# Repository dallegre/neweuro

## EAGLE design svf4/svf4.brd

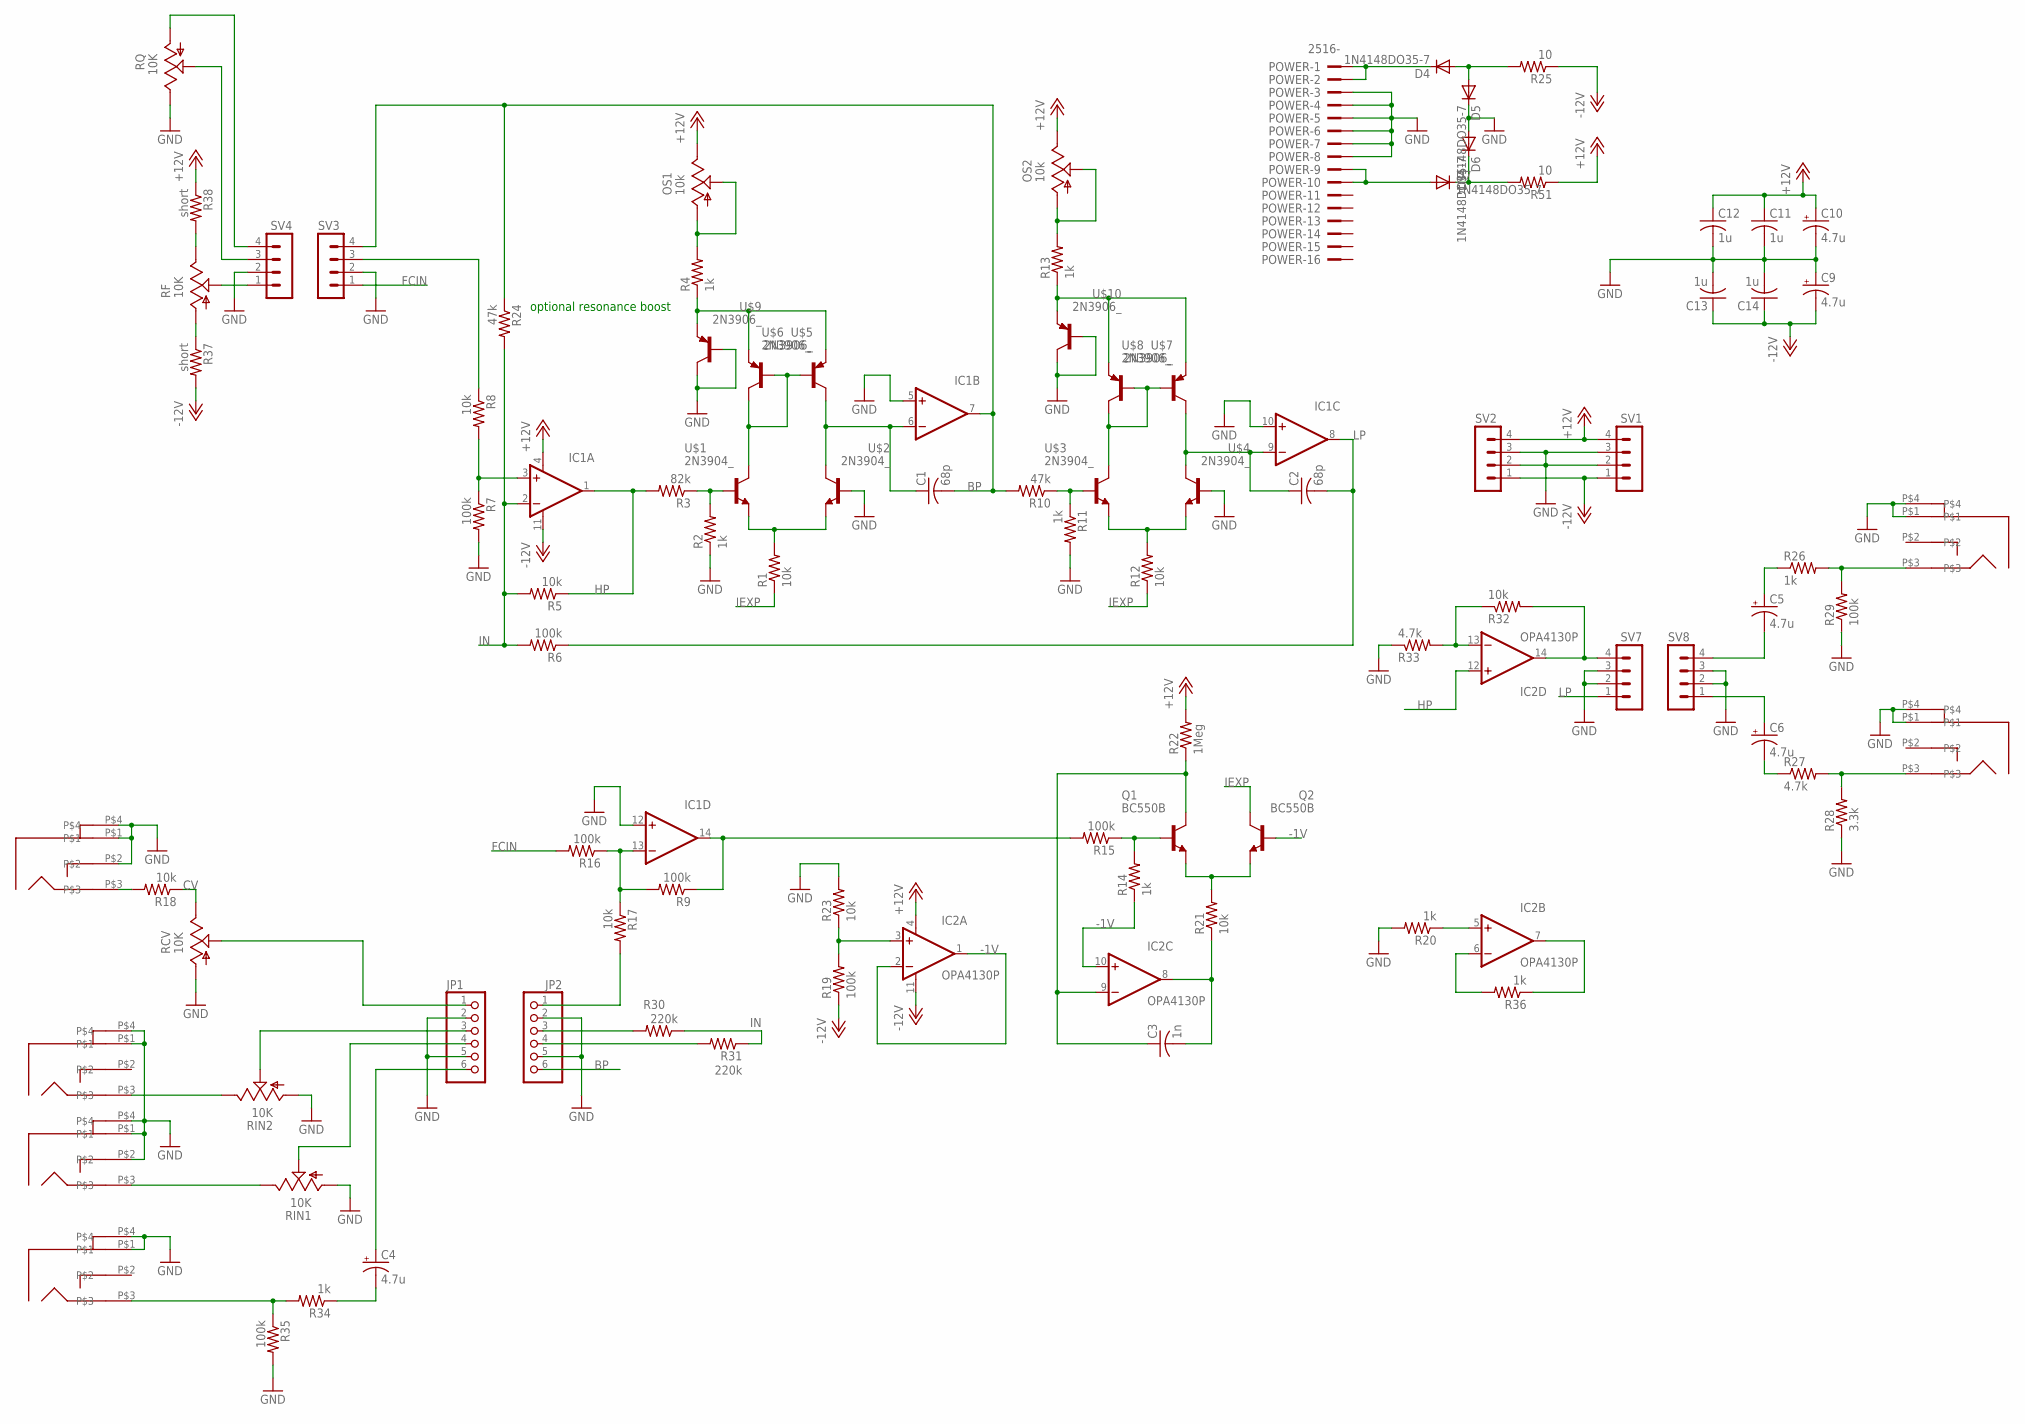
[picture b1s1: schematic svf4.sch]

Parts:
BPOUT: PJ301BM
C1, C2: 68p; C050-025X075
C3: 1n; C050-025X075
C4, C5, C6, C9, C10: 4.7u; E2,5-6
C11, C12, C13, C14: 1u; C050-025X075
CVIN: PJ301BM
D4, D5, D6, D7: 1N4148DO35-7; DO35-7
HPOUT: PJ301BM
IC1, IC2: OPA4130P; DIL14
IN, IN1: PJ301BM
JP1, JP2: PINHD-1X6; 1X06
LPOUT: PJ301BM
OS1, OS2: 10k; S64W
POWER: 2516-; PAK100/2500-16
Q1, Q2: BC550B; TO92-EBC
R1, R5, R8, R12, R17, R21, R23, R32: 10k; 0207/2V
R2, R4, R11, R13, R14, R20, R36: 1k; 0207/2V
R3: 82k; 0207/2V
R6, R7, R9, R15, R16, R19: 100k; 0207/2V
R10, R24: 47k; 0207/2V
R18: 10k; 0204/7
R22: 1Meg; 0207/2V
R25, R51: 10; 0207/2V
R26, R34: 1k; 0204/7
R27: 4.7k; 0204/7
R28: 3.3k; 0204/7
R29, R35: 100k; 0204/7
R30, R31: 220k; 0207/2V
R33: 4.7k; 0207/2V
R37, R38: short; 0204/7
RCV: 10K; EVUFXJ
RF: 10K; EVUFXJ
RIN1, RIN2: 10K; EVUFXJ
RQ: 10K; EVUFXJ
SV1, SV2, SV3, SV4, SV7, SV8: MA04-1
U$1, U$2, U$3, U$4: 2N3904_; TO92-EBC
U$5, U$6, U$7, U$8, U$9, U$10: 2N3906_; TO92-EBC

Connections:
+12V: C10.+, C11.1, C12.1, IC1.4 (V+), IC2.4 (V+), OS1.E, OS2.E, R22.2, R38.1, R51.1, SV1.4, SV2.4
-1V: IC2.1 (OUT), IC2.2 (-IN), IC2.10 (+IN), Q2.B, R14.1
-12V: C9.-, C13.1, C14.1, IC1.11 (V-), IC2.11 (V-), R19.1, R25.1, R37.2, SV1.1, SV2.1
BP: C1.2, IC1.7 (OUT), JP2.6, R10.2, R24.1, SV3.4
CV: R18.1, RCV.3 (E)
FCIN: R16.2, SV3.1
GND: BPOUT.P$1, BPOUT.P$4, C9.+, C10.-, C11.2, C12.2, C13.2, C14.2, CVIN.P$1, CVIN.P$2, CVIN.P$4, D5.C, D6.A, HPOUT.P$1, HPOUT.P$4, IC1.5 (+IN), IC1.10 (+IN), IC1.12 (+IN), IN.P$1, IN.P$2, IN.P$4, IN1.P$1, IN1.P$4, JP1.2, JP1.5, JP2.2, JP2.5, LPOUT.P$1, LPOUT.P$4, POWER.3, POWER.4, POWER.5, POWER.6, POWER.7, POWER.8, R2.1, R7.2, R11.2, R20.2, R23.2, R28.1, R29.1, R33.1, R35.2, RCV.1 (A), RIN1.1 (A), RIN2.1 (A), RQ.3 (E), SV1.2, SV1.3, SV2.2, SV2.3, SV3.2, SV4.2, SV7.2, SV7.3, SV8.2, SV8.3, U$2.B, U$4.B, U$9.B, U$9.E (C), U$10.B, U$10.E (C)
HP: IC1.1 (OUT), IC2.12 (+IN), R3.2, R5.1
IEXP: Q2.C, R1.1, R12.1
IN: IC1.2 (-IN), R5.2, R6.2, R24.2, R30.1, R31.1
LP: C2.2, IC1.8 (OUT), R6.1, SV7.1
LPOUT: LPOUT.P$3, R27.2, R28.2
unnamed: R12.2, U$3.C (E), U$4.C (E)
unnamed: OS1.A, OS1.S, R4.2
unnamed: R4.1, U$5.C (E), U$6.C (E), U$9.C (E)
unnamed: U$1.E (C), U$5.B, U$5.E (C), U$6.B
unnamed: R1.2, U$1.C (E), U$2.C (E)
unnamed: R2.2, R3.1, U$1.B
unnamed: IC2.7 (OUT), R36.1
unnamed: C6.+, SV8.1
unnamed: IC1.3 (+IN), R7.1, R8.2
unnamed: OS2.A, OS2.S, R13.2
unnamed: C1.1, IC1.6 (-IN), U$2.E (C), U$6.E (C)
unnamed: R8.1, SV3.3
unnamed: IC1.13 (-IN), R9.2, R16.1, R17.1
unnamed: U$3.E (C), U$7.B, U$7.E (C), U$8.B
unnamed: R10.1, R11.1, U$3.B
unnamed: JP2.1, R17.2
unnamed: R13.1, U$7.C (E), U$8.C (E), U$10.C (E)
unnamed: C2.1, IC1.9 (-IN), U$4.E (C), U$8.E (C)
unnamed: RF.2 (S), SV4.1
unnamed: D4.A, D5.A, R25.2
unnamed: Q1.B, R14.2, R15.1
unnamed: IC1.14 (OUT), R9.1, R15.2
unnamed: CVIN.P$3, R18.2
unnamed: Q1.E, Q2.E, R21.2
unnamed: RQ.1 (A), SV4.4
unnamed: C3.2, IC2.8 (OUT), R21.1
unnamed: D6.C, D7.C, R51.2
unnamed: C3.1, IC2.9 (-IN), Q1.C, R22.1
unnamed: IC2.3 (+IN), R19.2, R23.1
unnamed: JP1.1, RCV.2 (S)
unnamed: RQ.2 (S), SV4.3
unnamed: C5.-, SV8.4
unnamed: JP1.4, RIN1.2 (S)
unnamed: IN.P$3, RIN1.3 (E)
unnamed: HPOUT.P$3, R26.2, R29.2
unnamed: C4.+, JP1.6
unnamed: JP2.3, R30.2
unnamed: BPOUT.P$3, R34.2, R35.1
unnamed: IN1.P$3, RIN2.3 (E)
unnamed: JP1.3, RIN2.2 (S)
unnamed: IC2.14 (OUT), R32.2, SV7.4
unnamed: IC2.13 (-IN), R32.1, R33.2
unnamed: C6.-, R27.1
unnamed: C5.+, R26.1
unnamed: C4.-, R34.1
unnamed: JP2.4, R31.2
unnamed: IC2.5 (+IN), R20.1
unnamed: IC2.6 (-IN), R36.2
unnamed: R38.2, RF.3 (E)
unnamed: R37.1, RF.1 (A)
unnamed: D7.A, POWER.9, POWER.10
unnamed: D4.C, POWER.1, POWER.2

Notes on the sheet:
optional resonance boost

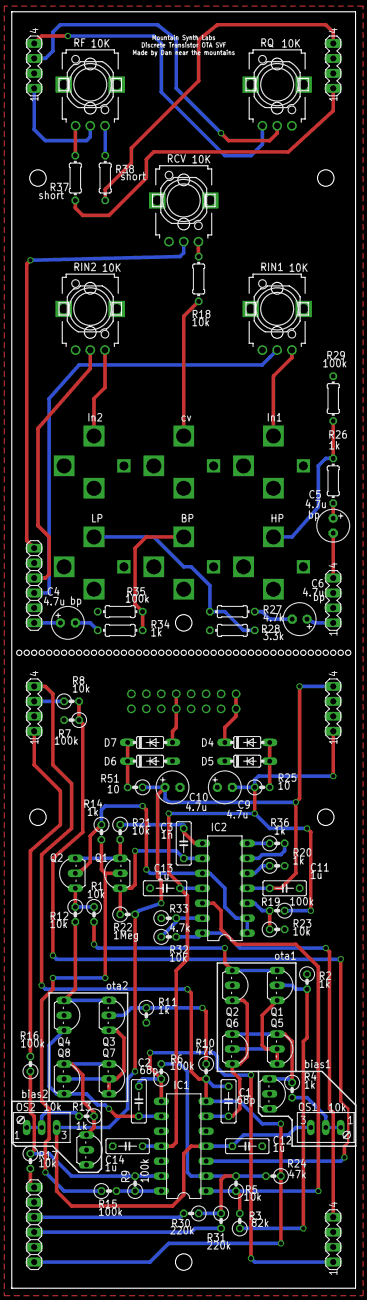
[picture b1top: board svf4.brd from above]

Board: 2 copper layers, 58.4 x 216.8 mm, 91 parts (1 on the bottom side), 64 nets.

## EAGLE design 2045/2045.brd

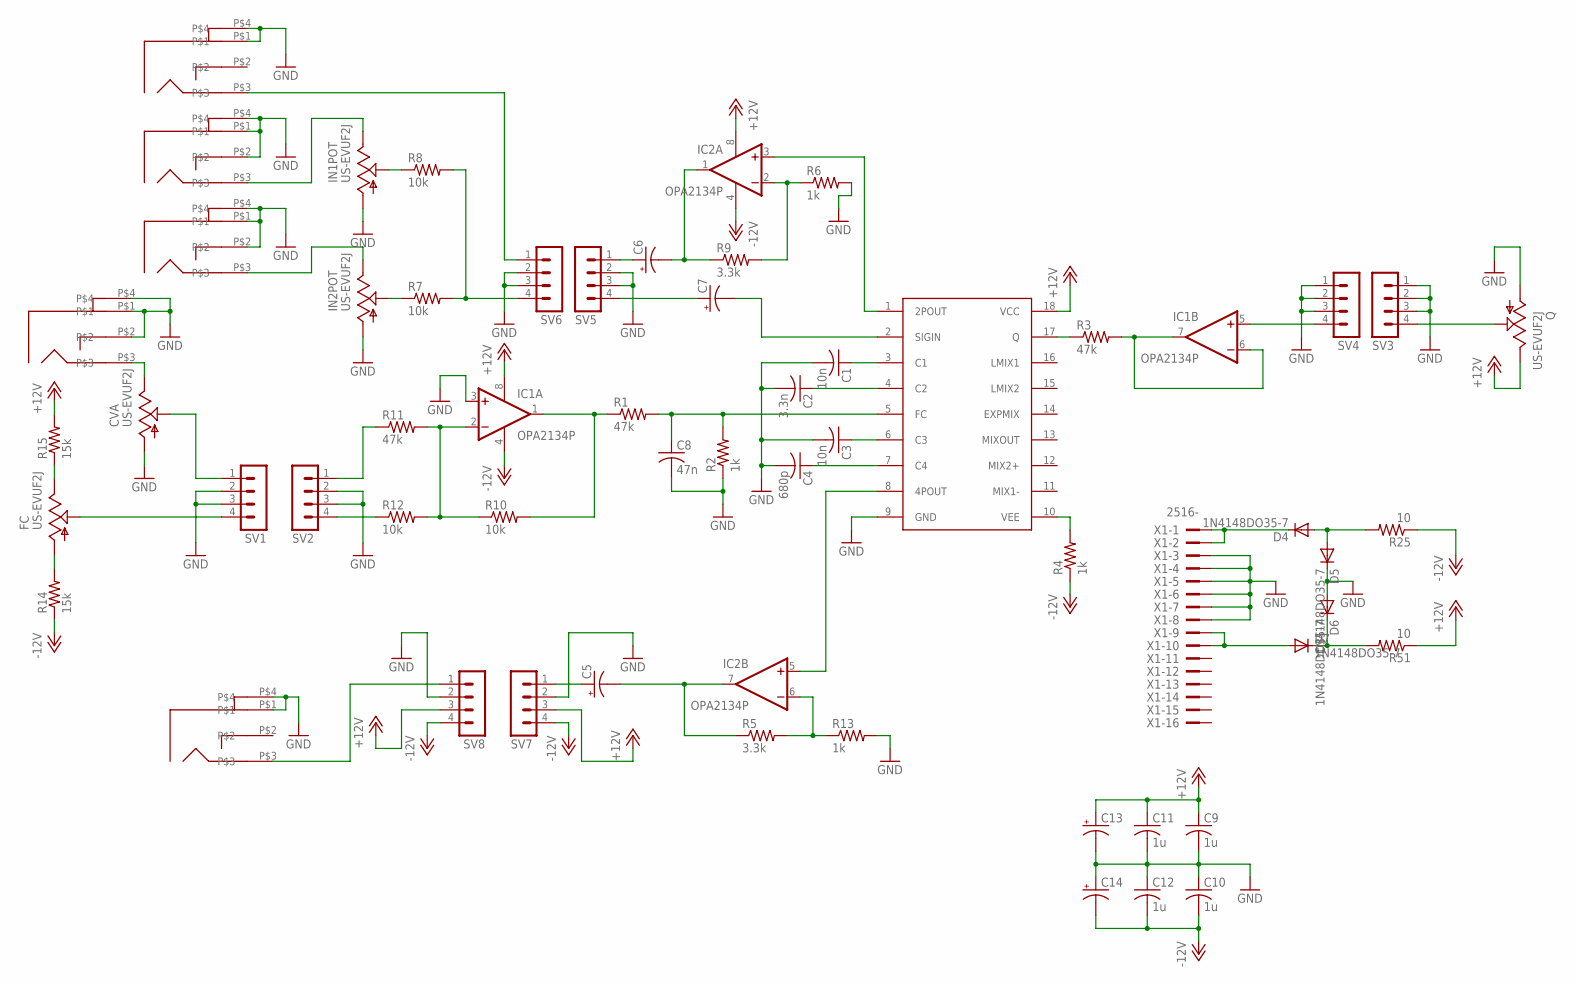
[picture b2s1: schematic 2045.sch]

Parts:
2POUT, 4POUTPUT: PJ301BM
C1, C3: 10n; C050-025X075
C2: 3.3n; C050-025X075
C4: 680p; C050-025X075
C5, C6, C7, C13, C14: CPOL-USE2.5-7; E2,5-7
C8: 47n; C050-025X075
C9, C10, C11, C12: 1u; C050-025X075
CVA: US-EVUF2J; EVUFXJ
CVIN: PJ301BM
D4, D5, D6, D7: 1N4148DO35-7; DO35-7
FC: US-EVUF2J; EVUFXJ
IC1, IC2: OPA2134P; DIL08
IN, IN2: PJ301BM
IN1POT, IN2POT: US-EVUF2J; EVUFXJ
Q: US-EVUF2J; EVUFXJ
R1, R3, R11: 47k; 0204/7
R2, R4, R6, R13: 1k; 0204/7
R5, R9: 3.3k; 0204/7
R7, R8, R10, R12: 10k; 0204/7
R14, R15: 15k; 0204/7
R25, R51: 10; 0207/2V
SV1, SV2, SV3, SV4, SV5, SV6, SV7, SV8: MA04-1
U$1: SSM2045; DIL18
X1: 2516-; PAK100/2500-16

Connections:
+12V: C9.1, C11.1, C13.+, IC1.8 (V+), IC2.8 (V+), Q.3 (E), R15.2, R51.1, SV7.3, SV8.3, U$1.18 (VCC)
-12V: C10.2, C12.2, C14.-, IC1.4 (V-), IC2.4 (V-), R4.1, R14.1, R25.1, SV7.4, SV8.4
GND: 2POUT.P$1, 2POUT.P$4, 4POUTPUT.P$1, 4POUTPUT.P$4, C1.2, C2.2, C3.2, C4.2, C8.2, C9.2, C10.1, C11.2, C12.1, C13.-, C14.+, CVA.1 (A), CVIN.P$1, CVIN.P$2, CVIN.P$4, D5.C, D6.A, IC1.3 (+IN), IN.P$1, IN.P$2, IN.P$4, IN1POT.1 (A), IN2.P$1, IN2.P$2, IN2.P$4, IN2POT.1 (A), Q.1 (A), R2.1, R6.2, R13.2, SV1.2, SV1.3, SV2.2, SV2.3, SV3.1, SV3.2, SV3.3, SV4.1, SV4.2, SV4.3, SV5.2, SV5.3, SV6.2, SV6.3, SV7.2, SV8.2, U$1.9 (GND), X1.3, X1.4, X1.5, X1.6, X1.7, X1.8
unnamed: C1.1, U$1.3 (C1)
unnamed: C2.1, U$1.4 (C2)
unnamed: C3.1, U$1.6 (C3)
unnamed: C4.1, U$1.7 (C4)
unnamed: FC.2 (S), SV1.4
unnamed: FC.1 (A), R14.2
unnamed: FC.3 (E), R15.1
unnamed: C8.1, R1.2, R2.2, U$1.5 (FC)
unnamed: R3.1, U$1.17 (Q)
unnamed: R4.2, U$1.10 (VEE)
unnamed: IC2.3 (+IN), U$1.1 (2POUT)
unnamed: IC2.2 (-IN), R6.1, R9.2
unnamed: IC2.5 (+IN), U$1.8 (4POUT)
unnamed: C5.-, IC2.7 (OUT), R5.1
unnamed: IN1POT.2 (S), R8.1
unnamed: C7.-, U$1.2 (SIGIN)
unnamed: R12.1, SV2.4
unnamed: IC1.2 (-IN), R10.1, R11.2, R12.2
unnamed: IC1.1 (OUT), R1.1, R10.2
unnamed: IC1.6 (-IN), IC1.7 (OUT), R3.2
unnamed: R11.1, SV2.1
unnamed: CVA.3 (E), CVIN.P$3
unnamed: Q.2 (S), SV3.4
unnamed: C7.+, SV5.4
unnamed: C6.+, SV5.1
unnamed: 2POUT.P$3, SV6.1
unnamed: R7.2, R8.2, SV6.4
unnamed: C5.+, SV7.1
unnamed: IN2POT.2 (S), R7.1
unnamed: IC1.5 (+IN), SV4.4
unnamed: CVA.2 (S), SV1.1
unnamed: 4POUTPUT.P$3, SV8.1
unnamed: IC2.6 (-IN), R5.2, R13.1
unnamed: C6.-, IC2.1 (OUT), R9.1
unnamed: IN.P$3, IN1POT.3 (E)
unnamed: IN2.P$3, IN2POT.3 (E)
unnamed: D6.C, D7.C, R51.2
unnamed: D4.A, D5.A, R25.2
unnamed: D7.A, X1.9, X1.10
unnamed: D4.C, X1.1, X1.2

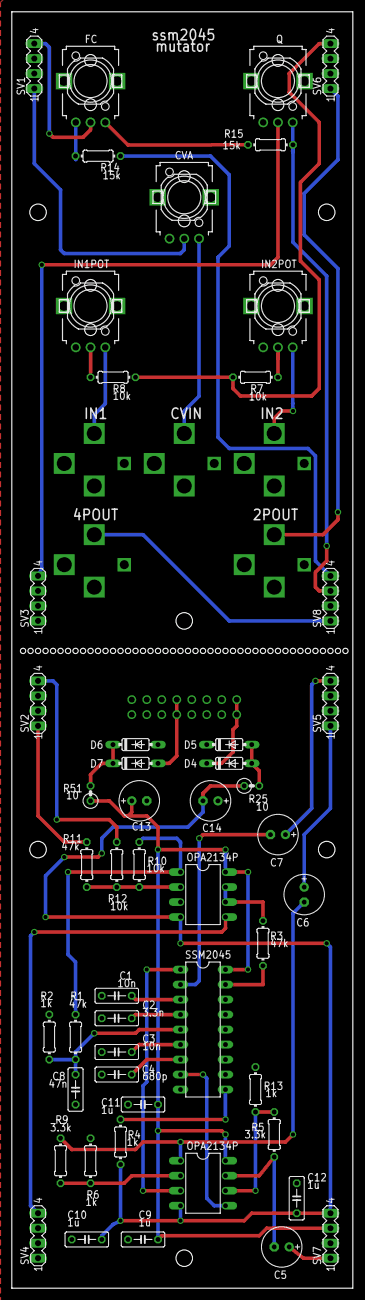
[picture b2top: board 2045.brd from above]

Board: 2 copper layers, 57.8 x 216.2 mm, 57 parts (1 on the bottom side), 43 nets.

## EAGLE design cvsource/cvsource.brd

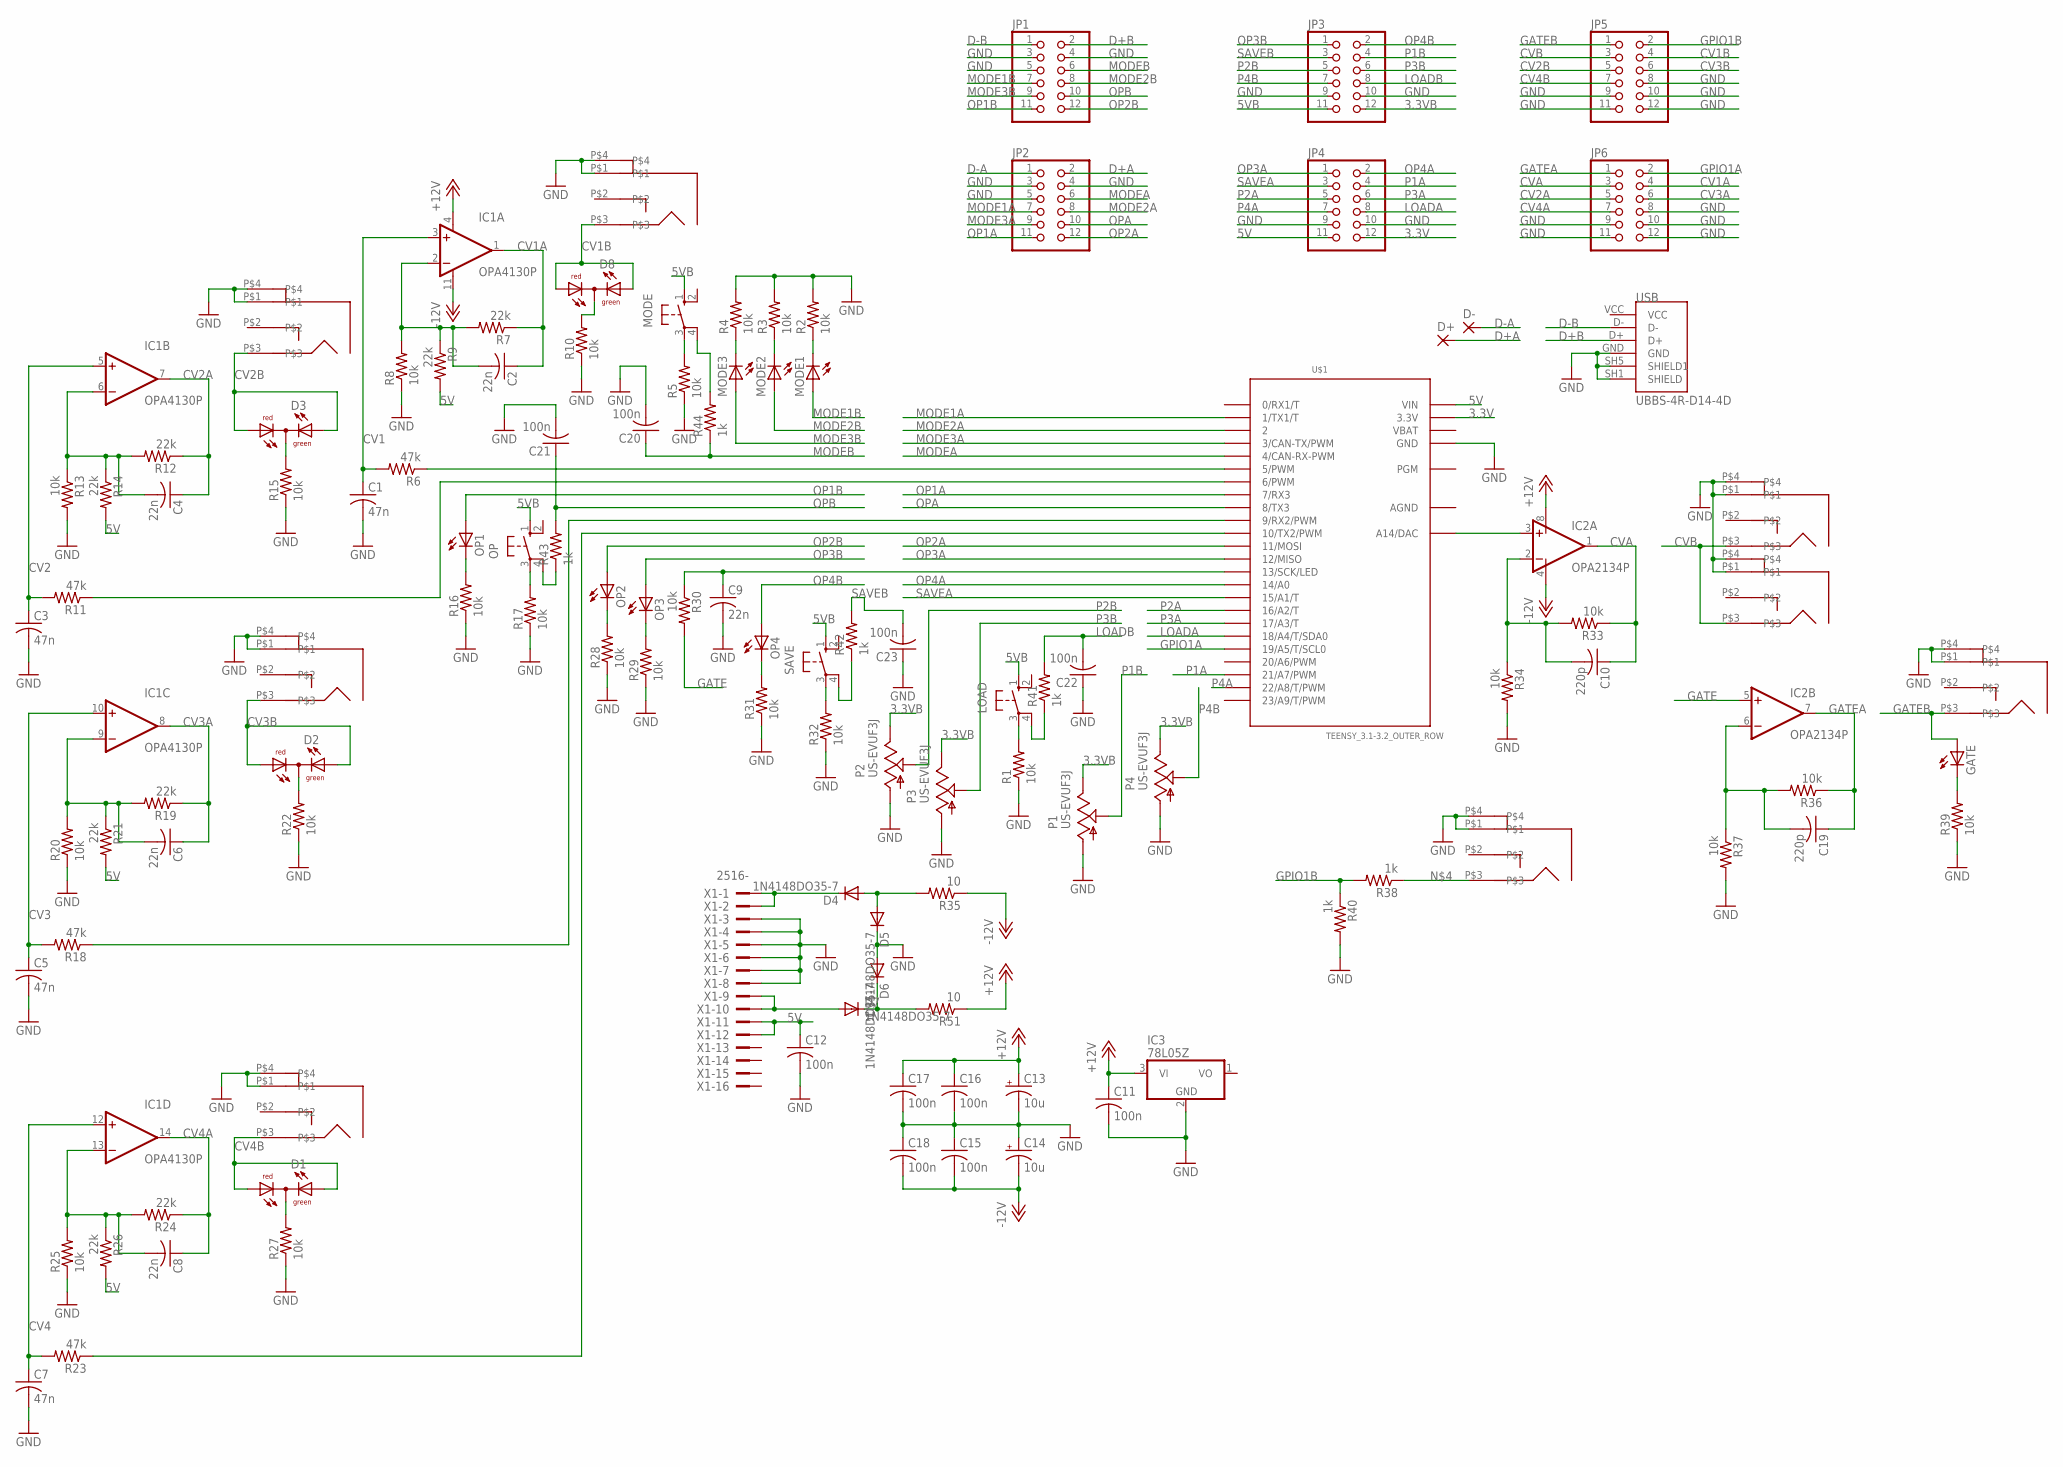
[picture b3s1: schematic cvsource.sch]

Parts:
C1, C3, C5, C7: 47n; C075-032X103
C2, C4, C6, C8, C9: 22n; C075-032X103
C10, C19: 220p; C075-032X103
C11, C12, C15, C16, C17, C18, C20, C21, C22, C23: 100n; C075-032X103
C13, C14: 10u; E5-10,5
CVOUT, CVOUT1, CVOUT2, CVOUT3, CVOUT4, CVOUT5, CVOUT6, CVOUT7: PJ301BM
D1, D2, D3, D8: DUOLED5MM
D4, D5, D6, D7: 1N4148DO35-7; DO35-7
D+: 2,0/0,9-R
D-: 2,0/0,9-R
GATE: LED5MM
IC1: OPA4130P; DIL14
IC2: OPA2134P; DIL08
IC3: 78L05Z; TO92
JP1, JP2, JP3, JP4, JP5, JP6: PINHD-2X6; 2X06
LOAD: 40-XX; B3F-40XX
MODE: 40-XX; B3F-40XX
MODE1, MODE2, MODE3: LED5MM
OP: 40-XX; B3F-40XX
OP1, OP2, OP3, OP4: LED5MM
P1, P2, P3, P4: US-EVUF3J; EVUFXJ
R1, R2, R3, R4, R5, R8, R10, R13, R15, R16, R17, R20, R22, R25, R27, R28, R29, R30, R31, R32, R33, R34, R36, R37, R39: 10k; 0207/2V
R6, R11, R18, R23: 47k; 0207/2V
R7, R9, R12, R14, R19, R21, R24, R26: 22k; 0207/2V
R35, R51: 10; 0207/2V
R38, R40, R41, R42, R43, R44: 1k; 0207/2V
SAVE: 40-XX; B3F-40XX
U$1: TEENSY_3.1-3.2_OUTER_ROW; TEENSY_3.0-3.2&LC_OUTER_ROW
USB: UBBS-4R-D14-4D; JST_UBBS-4R-D14-4D
X1: 2516-; PAK100/2500-16

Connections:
3.3V: JP4.12, U$1.3.3V, U$1.3.3V1 (3.3V)
3.3VB: JP3.12, P1.3 (E), P2.3 (E), P3.3 (E), P4.3 (E)
5V: C12.1, JP4.11, R9.2, R14.2, R21.2, R26.2, U$1.VIN, X1.11, X1.12
5VB: JP3.11, LOAD.1 (S), MODE.1 (S), OP.1 (S), SAVE.1 (S)
+12V: C11.1, C13.+, C16.1, C17.1, IC1.4 (V+), IC2.8 (V+), IC3.3 (VI), R51.1
-12V: C14.-, C15.2, C18.2, IC1.11 (V-), IC2.4 (V-), R35.1
AGND: U$1.AGND
CV1: C1.1, IC1.3 (+IN), R6.2
CV1A: C2.1, IC1.1 (OUT), JP6.4, R7.1
CV1B: CVOUT1.P$3, D8.AG, D8.AR, JP5.4
CV2: C3.1, IC1.5 (+IN), R11.2
CV2A: C4.1, IC1.7 (OUT), JP6.5, R12.1
CV2B: CVOUT2.P$3, D3.AG, D3.AR, JP5.5
CV3: C5.1, IC1.10 (+IN), R18.2
CV3A: C6.1, IC1.8 (OUT), JP6.6, R19.1
CV3B: CVOUT3.P$3, D2.AG, D2.AR, JP5.6
CV4: C7.1, IC1.12 (+IN), R23.2
CV4A: C8.1, IC1.14 (OUT), JP6.7, R24.1
CV4B: CVOUT4.P$3, D1.AG, D1.AR, JP5.7
CVA: C10.1, IC2.1 (OUT), JP6.3, R33.1
CVB: CVOUT.P$3, CVOUT6.P$3, JP5.3
D+A: D+.1, JP2.2
D+B: JP1.2, USB.D+
D-A: D-.1, JP2.1
D-B: JP1.1, USB.D-
GATE: IC2.5 (+IN), R30.2
GATEA: C19.1, IC2.7 (OUT), JP6.1, R36.1
GATEB: CVOUT5.P$3, GATE.A, JP5.1
GND: C1.2, C3.2, C5.2, C7.2, C9.2, C11.2, C12.2, C13.-, C14.+, C15.1, C16.2, C17.2, C18.1, C20.2, C21.2, C22.1, C23.1, CVOUT.P$1, CVOUT.P$4, CVOUT1.P$1, CVOUT1.P$4, CVOUT2.P$1, CVOUT2.P$4, CVOUT3.P$1, CVOUT3.P$4, CVOUT4.P$1, CVOUT4.P$4, CVOUT5.P$1, CVOUT5.P$4, CVOUT6.P$1, CVOUT6.P$4, CVOUT7.P$1, CVOUT7.P$4, D5.C, D6.A, IC3.2 (GND), JP1.3, JP1.4, JP1.5, JP2.3, JP2.4, JP2.5, JP3.9, JP3.10, JP4.9, JP4.10, JP5.8, JP5.9, JP5.10, JP5.11, JP5.12, JP6.8, JP6.9, JP6.10, JP6.11, JP6.12, P1.1 (A), P2.1 (A), P3.1 (A), P4.1 (A), R1.1, R2.2, R3.2, R4.2, R5.1, R8.1, R10.1, R13.2, R15.1, R16.1, R17.1, R20.1, R22.1, R25.1, R27.1, R28.1, R29.1, R31.1, R32.1, R34.2, R37.2, R39.1, R40.2, U$1.GND, U$1.GND1 (GND), USB.GND, USB.SH1 (SHIELD), USB.SH5 (SHIELD1), X1.3, X1.4, X1.5, X1.6, X1.7, X1.8
GPIO1A: JP6.2, U$1.19/A5 (19/A5/T/SCL0)
GPIO1B: JP5.2, R38.2, R40.1
LOADA: JP4.8, U$1.18/A4 (18/A4/T/SDA0)
LOADB: C22.2, JP3.8, R41.2
MODE1A: JP2.7, U$1.1 (1/TX1/T)
MODE1B: JP1.7, MODE1.A
MODE2A: JP2.8, U$1.2
MODE2B: JP1.8, MODE2.A
MODE3A: JP2.9, U$1.3 (3/CAN-TX/PWM)
MODE3B: JP1.9, MODE3.A
MODEA: JP2.6, U$1.4 (4/CAN-RX-PWM)
MODEB: C20.1, JP1.6, R44.1
unnamed: MODE1.K (C), R2.1
unnamed: MODE2.K (C), R3.1
unnamed: MODE3.K (C), R4.1
unnamed: CVOUT7.P$3, R38.1
unnamed: C19.2, IC2.6 (-IN), R36.2, R37.1
unnamed: GATE.K (C), R39.2
unnamed: LOAD.4 (P1), R41.1
unnamed: MODE.3, R5.2
unnamed: R6.1, U$1.5 (5/PWM)
unnamed: OP1.K (C), R16.2
unnamed: C2.2, IC1.2 (-IN), R7.2, R8.2, R9.1
unnamed: R42.1, SAVE.4 (P1)
unnamed: D8.K (C), R10.2
unnamed: R11.1, U$1.6 (6/PWM)
unnamed: C4.2, IC1.6 (-IN), R12.2, R13.1, R14.1
unnamed: OP.4 (P1), R43.1
unnamed: D3.K (C), R15.2
unnamed: MODE.4 (P1), R44.2
unnamed: D1.K (C), R27.2
unnamed: OP.3, R17.2
unnamed: R18.1, U$1.9 (9/RX2/PWM)
unnamed: C6.2, IC1.9 (-IN), R19.2, R20.2, R21.1
unnamed: D2.K (C), R22.2
unnamed: OP4.K (C), R31.2
unnamed: R23.1, U$1.10 (10/TX2/PWM)
unnamed: C8.2, IC1.13 (-IN), R24.2, R25.2, R26.1
unnamed: OP2.K (C), R28.2
unnamed: OP3.K (C), R29.2
unnamed: C9.1, R30.1, U$1.13 (13/SCK/LED)
unnamed: R32.2, SAVE.3
unnamed: LOAD.3, R1.2
unnamed: IC2.3 (+IN), U$1.RESET/DAC (A14/DAC)
unnamed: C10.2, IC2.2 (-IN), R33.2, R34.1
unnamed: D6.C, D7.C, R51.2
unnamed: D4.A, D5.A, R35.2
unnamed: D7.A, X1.9, X1.10
unnamed: D4.C, X1.1, X1.2
OP1A: JP2.11, U$1.7 (7/RX3)
OP1B: JP1.11, OP1.A
OP2A: JP2.12, U$1.11 (11/MOSI)
OP2B: JP1.12, OP2.A
OP3A: JP4.1, U$1.12 (12/MISO)
OP3B: JP3.1, OP3.A
OP4A: JP4.2, U$1.14/A0
OP4B: JP3.2, OP4.A
OPA: JP2.10, U$1.8 (8/TX3)
OPB: C21.1, JP1.10, R43.2
P1A: JP4.4, U$1.21/A7 (21/A7/PWM)
P1B: JP3.4, P1.2 (S)
P2A: JP4.5, U$1.16/A2 (16/A2/T)
P2B: JP3.5, P2.2 (S)
P3A: JP4.6, U$1.17/A3 (17/A3/T)
P3B: JP3.6, P3.2 (S)
P4A: JP4.7, U$1.22/A8 (22/A8/T/PWM)
P4B: JP3.7, P4.2 (S)
SAVEA: JP4.3, U$1.15/A1 (15/A1/T)
SAVEB: C23.2, JP3.3, R42.2
VBAT: U$1.VBAT

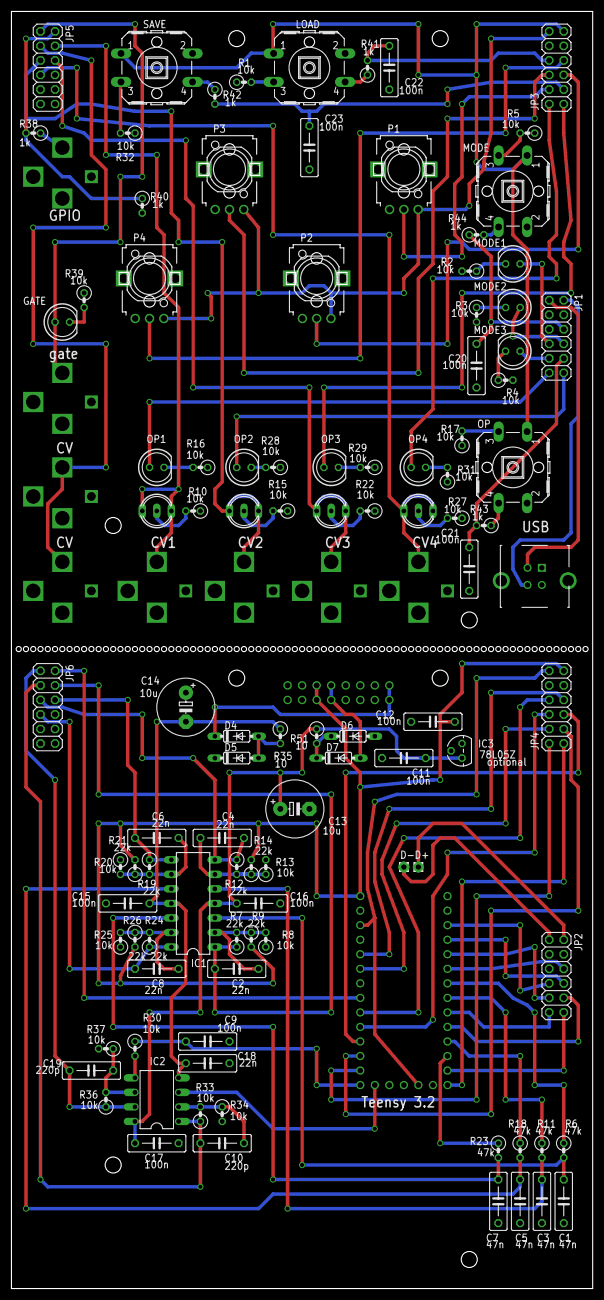
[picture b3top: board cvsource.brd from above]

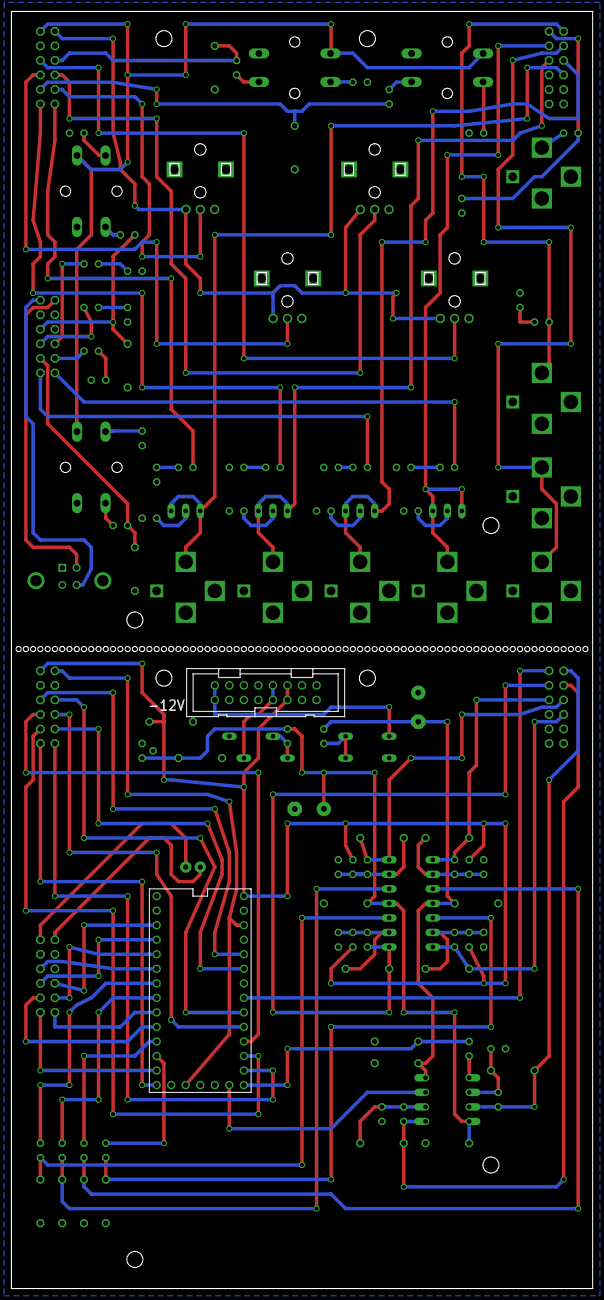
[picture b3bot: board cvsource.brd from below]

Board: 2 copper layers, 101.6 x 223.2 mm, 114 parts (2 on the bottom side), 97 nets.

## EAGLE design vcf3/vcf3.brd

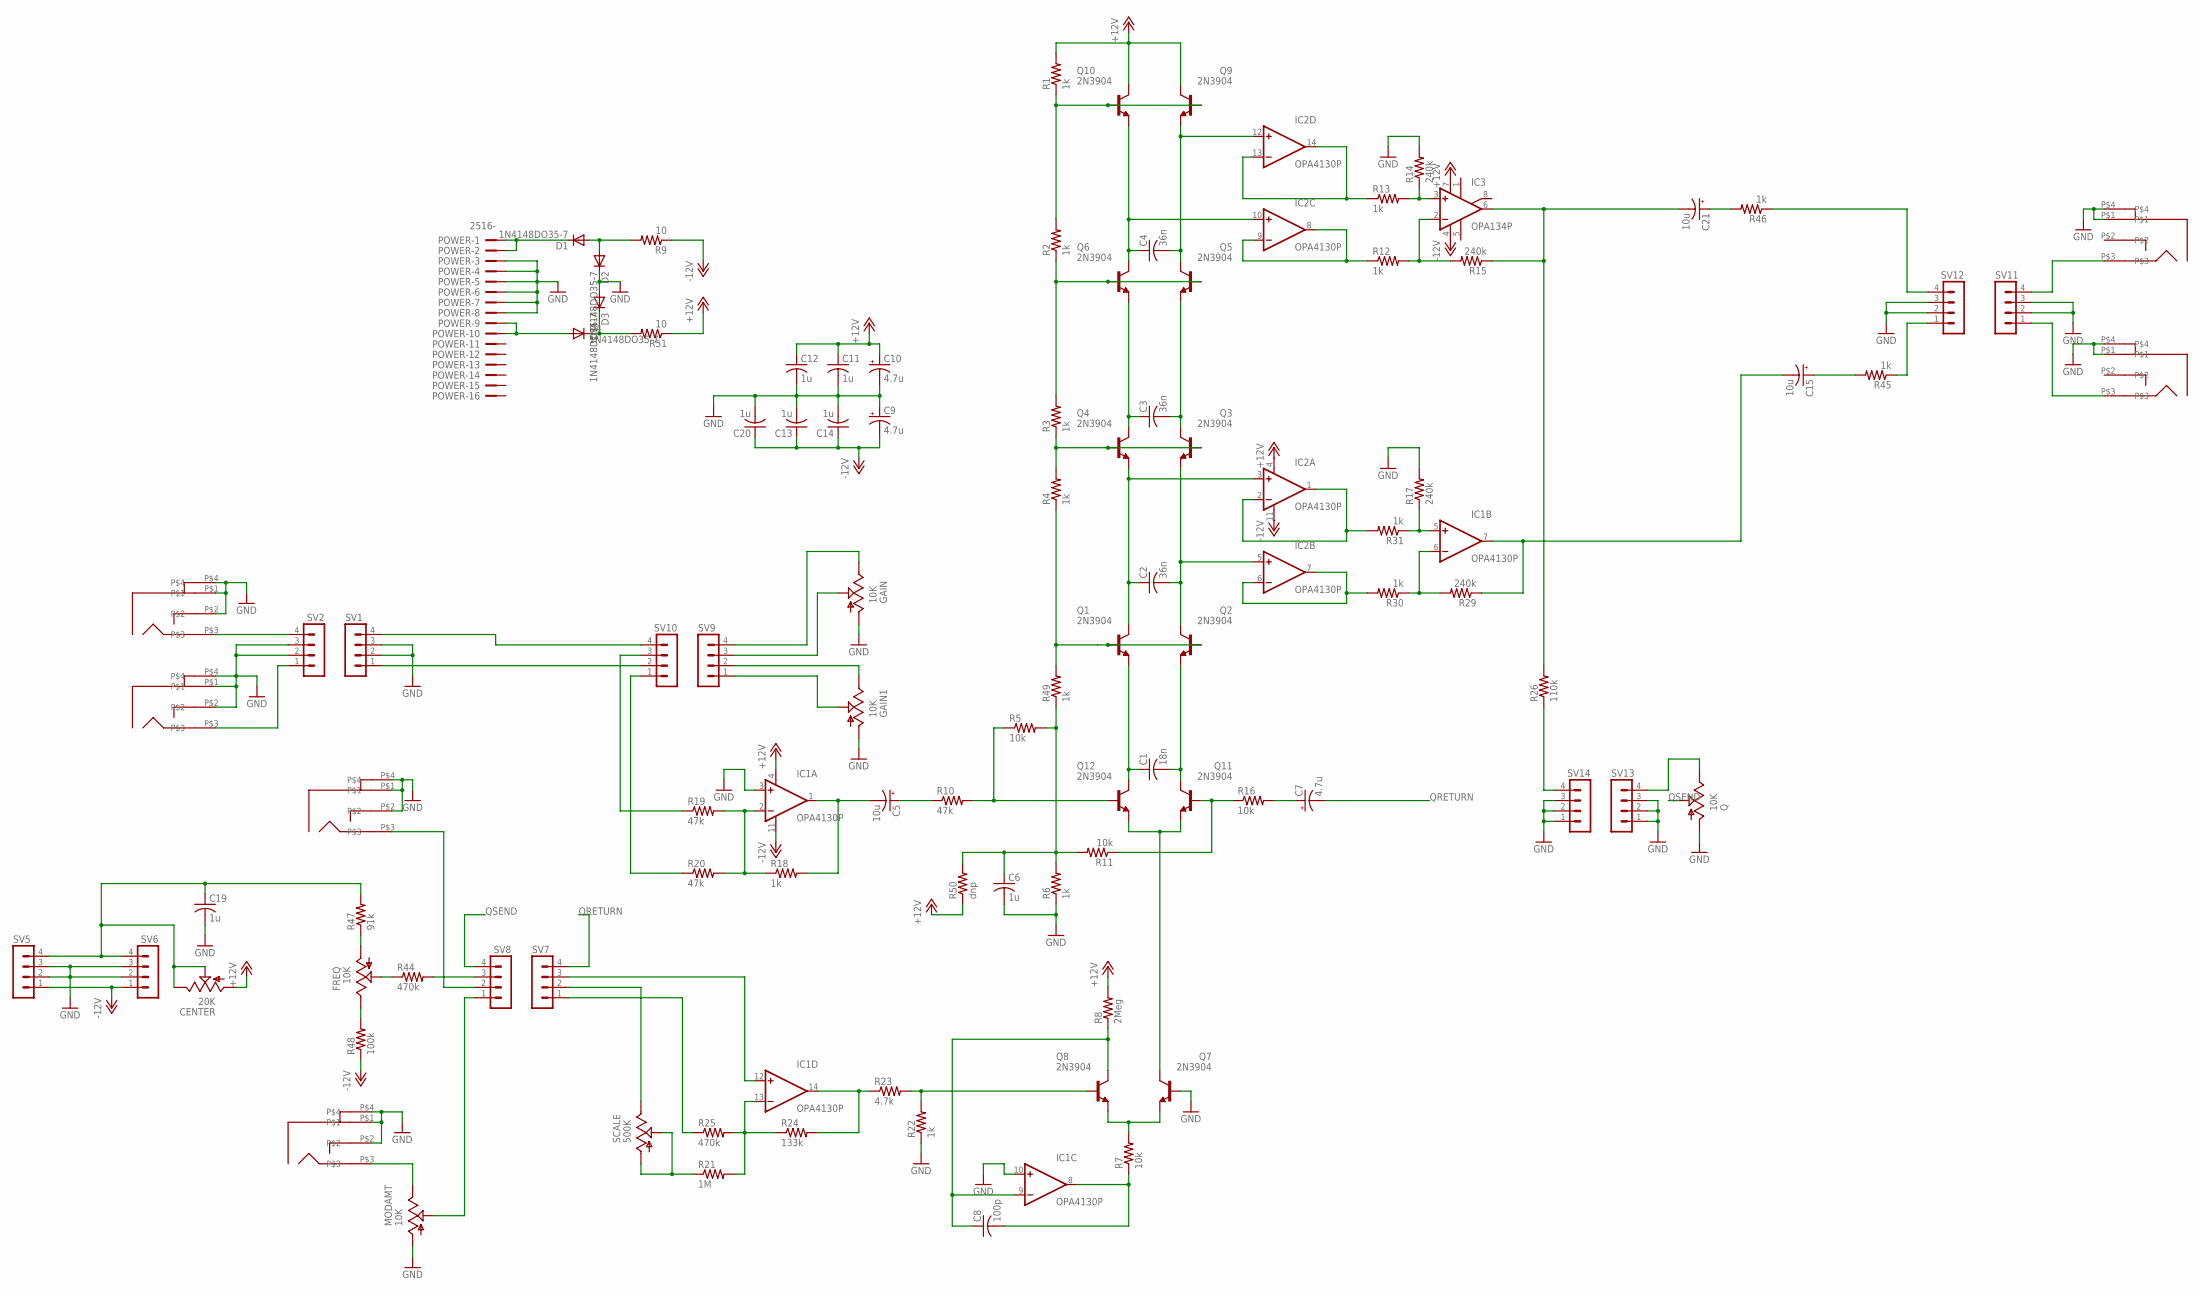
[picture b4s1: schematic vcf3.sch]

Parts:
AIN, AIN2: PJ301BM
BP: PJ301BM
C1: 18n; C050-025X075
C2, C3, C4: 36n; C050-025X075
C5, C15, C21: 10u; E2,5-6
C6, C11, C12, C13, C14, C19, C20: 1u; C050-025X075
C7, C9, C10: 4.7u; E2,5-6
C8: 100p; C050-025X075
CENTER: 20K; S64W
D1, D2, D3, D4: 1N4148DO35-7; DO35-7
FREQ: 10K; EVUFXJ
GAIN, GAIN1: 10K; EVUFXJ
IC1, IC2: OPA4130P; DIL14
IC3: OPA134P; DIL08
LP: PJ301BM
MIN, MIN1: PJ301BM
MODAMT: 10K; EVUFXJ
POWER: 2516-; PAK100/2500-16
Q: 10K; EVUFXJ
Q1, Q2, Q3, Q4, Q5, Q6, Q7, Q8, Q9, Q10, Q11, Q12: 2N3904; TO92
R1, R2, R3, R4, R6, R12, R13, R18, R22, R30, R31, R45, R46, R49: 1k; 0207/2V
R5, R7, R11, R16: 10k; 0207/2V
R8: 2Meg; 0207/2V
R9, R51: 10; 0207/2V
R10, R19, R20: 47k; 0207/2V
R14, R15, R17, R29: 240k; 0207/2V
R21: 1M; 0207/2V
R23: 4.7k; 0207/2V
R24: 133k; 0207/2V
R25: 470k; 0207/2V
R26: 110k; 0207/2V
R44: 470k; 0204/7
R47: 91k; 0204/7
R48: 100k; 0204/7
R50: dnp; 0207/2V
SCALE: 500K; S64W
SV1, SV2, SV5, SV6, SV7, SV8, SV9, SV10, SV11, SV12, SV13, SV14: MA04-1

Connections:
+12V: C10.+, C11.1, C12.1, CENTER.A, IC1.4 (V+), IC2.4 (V+), IC3.7 (V+), Q9.1 (C), Q10.1 (C), R1.2, R8.2, R50.1, R51.1
-12V: C9.-, C13.1, C14.1, C20.1, IC1.11 (V-), IC2.11 (V-), IC3.4 (V-), R9.1, R48.1, SV5.1, SV6.1
GND: AIN.P$1, AIN.P$2, AIN.P$4, AIN2.P$1, AIN2.P$2, AIN2.P$4, BP.P$1, BP.P$4, C6.2, C9.+, C10.-, C11.2, C12.2, C13.2, C14.2, C19.2, C20.2, D2.C, D3.A, GAIN.1 (A), GAIN1.1 (A), IC1.3 (+IN), IC1.10 (+IN), LP.P$1, LP.P$4, MIN.P$1, MIN.P$2, MIN.P$4, MIN1.P$1, MIN1.P$2, MIN1.P$4, MODAMT.1 (A), POWER.3, POWER.4, POWER.5, POWER.6, POWER.7, POWER.8, Q.1 (A), Q7.2 (B), R6.1, R14.2, R17.2, R22.1, SV1.2, SV1.3, SV2.2, SV2.3, SV5.2, SV5.3, SV6.2, SV6.3, SV11.2, SV11.3, SV12.2, SV12.3, SV13.1, SV13.2, SV13.3, SV14.1, SV14.2, SV14.3
unnamed: Q7.1 (C), Q11.3 (E), Q12.3 (E)
unnamed: C1.1, Q1.3 (E), Q12.1 (C)
unnamed: C2.1, IC2.3 (+IN), Q1.1 (C), Q4.3 (E)
unnamed: C3.1, Q4.1 (C), Q6.3 (E)
unnamed: C3.2, Q3.1 (C), Q5.3 (E)
unnamed: C2.2, IC2.5 (+IN), Q2.1 (C), Q3.3 (E)
unnamed: C1.2, Q2.3 (E), Q11.1 (C)
unnamed: C4.2, IC2.12 (+IN), Q5.1 (C), Q9.3 (E)
unnamed: C4.1, IC2.10 (+IN), Q6.1 (C), Q10.3 (E)
unnamed: Q9.2 (B), Q10.2 (B), R1.1, R2.2
unnamed: Q5.2 (B), Q6.2 (B), R2.1, R3.2
unnamed: Q3.2 (B), Q4.2 (B), R3.1, R4.2
unnamed: Q1.2 (B), Q2.2 (B), R4.1, R49.2
unnamed: Q12.2 (B), R5.1, R10.2
unnamed: IC1.2 (-IN), R18.1, R19.2, R20.2
unnamed: Q7.3 (E), Q8.3 (E), R7.2
unnamed: C8.2, IC1.8 (OUT), R7.1
unnamed: MIN.P$3, MODAMT.3 (E)
unnamed: C8.1, IC1.9 (-IN), Q8.1 (C), R8.1
unnamed: C5.-, IC1.1 (OUT), R18.2
unnamed: C5.+, R10.1
unnamed: Q11.2 (B), R11.1, R16.1
unnamed: IC2.13 (-IN), IC2.14 (OUT), R13.1
unnamed: IC1.12 (+IN), SV7.3
unnamed: IC3.2 (-IN), R12.2, R15.2
unnamed: IC3.3 (+IN), R13.2, R14.1
unnamed: D3.C, D4.C, R51.2
unnamed: MIN1.P$3, SV8.2
unnamed: D1.A, D2.A, R9.2
unnamed: SV1.1, SV10.2
unnamed: C7.+, R16.2
unnamed: R26.1, SV14.4
unnamed: R21.1, SCALE.A, SCALE.S
unnamed: Q8.2 (B), R22.2, R23.2
unnamed: IC2.8 (OUT), IC2.9 (-IN), R12.1
unnamed: IC1.13 (-IN), R21.2, R24.1, R25.2
unnamed: IC2.1 (OUT), IC2.2 (-IN), R31.2
unnamed: SCALE.E, SV7.2
unnamed: C15.+, R45.2
unnamed: C19.1, CENTER.E, CENTER.S, R47.2, SV5.4, SV6.4
unnamed: R19.1, SV10.3
unnamed: IC2.6 (-IN), IC2.7 (OUT), R30.2
unnamed: IC1.5 (+IN), R17.1, R31.1
unnamed: IC1.6 (-IN), R29.2, R30.1
unnamed: C15.-, IC1.7 (OUT), R29.1
unnamed: R45.1, SV12.1
unnamed: MODAMT.2 (S), SV8.1
unnamed: C21.-, IC3.6 (OUT), R15.1, R26.2
unnamed: IC1.14 (OUT), R23.1, R24.2
unnamed: GAIN1.3 (E), SV9.2
unnamed: FREQ.1 (A), R47.1
unnamed: SV1.4, SV10.4
unnamed: C21.+, R46.2
unnamed: R46.1, SV12.4
unnamed: FREQ.2 (S), R44.1
unnamed: FREQ.3 (E), R48.2
unnamed: C6.1, R5.2, R6.2, R11.2, R49.1, R50.2
unnamed: D4.A, POWER.9, POWER.10
unnamed: D1.C, POWER.1, POWER.2
unnamed: AIN.P$3, SV2.4
unnamed: AIN2.P$3, SV2.1
unnamed: R44.2, SV8.3
unnamed: R25.1, SV7.1
unnamed: BP.P$3, SV11.1
unnamed: LP.P$3, SV11.4
unnamed: R20.1, SV10.1
unnamed: GAIN.3 (E), SV9.4
unnamed: GAIN.2 (S), SV9.3
unnamed: GAIN1.2 (S), SV9.1
unnamed: Q.3 (E), SV13.4
QRETURN: C7.-, SV7.4
QSEND: Q.2 (S), SV8.4

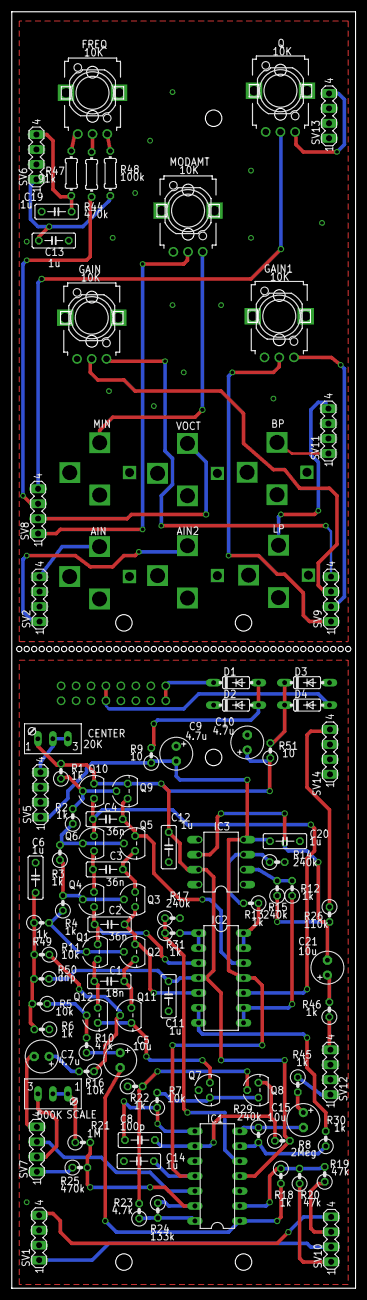
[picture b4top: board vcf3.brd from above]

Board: 2 copper layers, 58.4 x 216.8 mm, 100 parts (1 on the bottom side), 75 nets.
